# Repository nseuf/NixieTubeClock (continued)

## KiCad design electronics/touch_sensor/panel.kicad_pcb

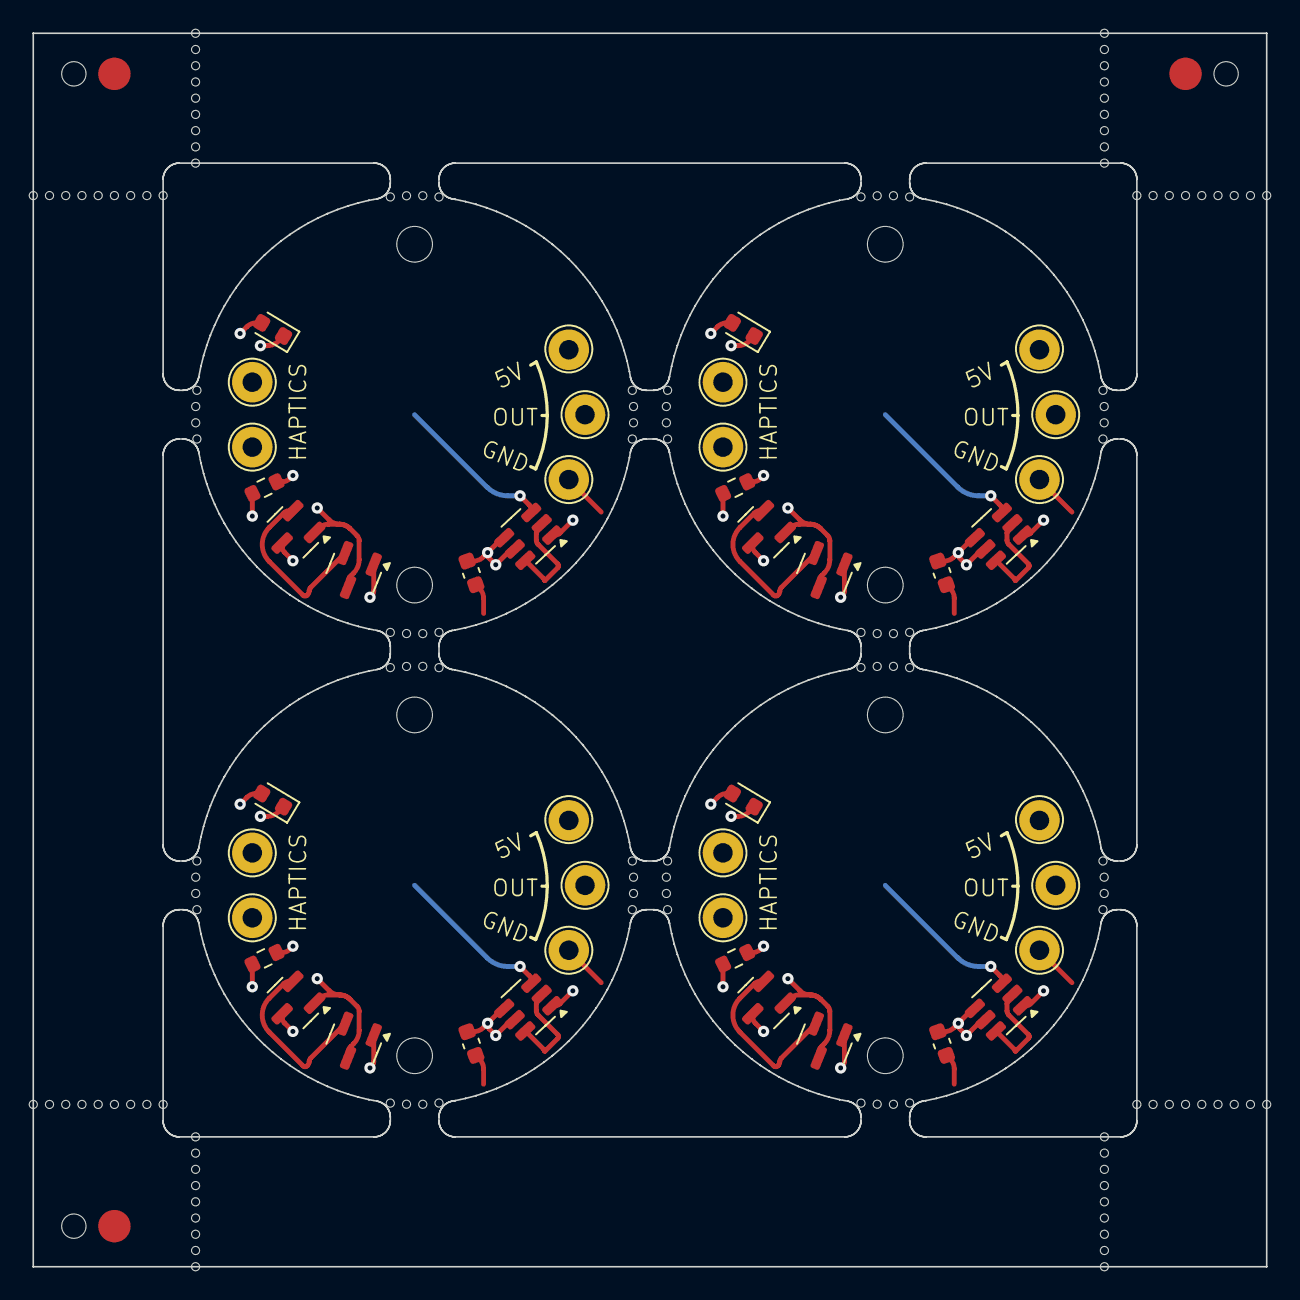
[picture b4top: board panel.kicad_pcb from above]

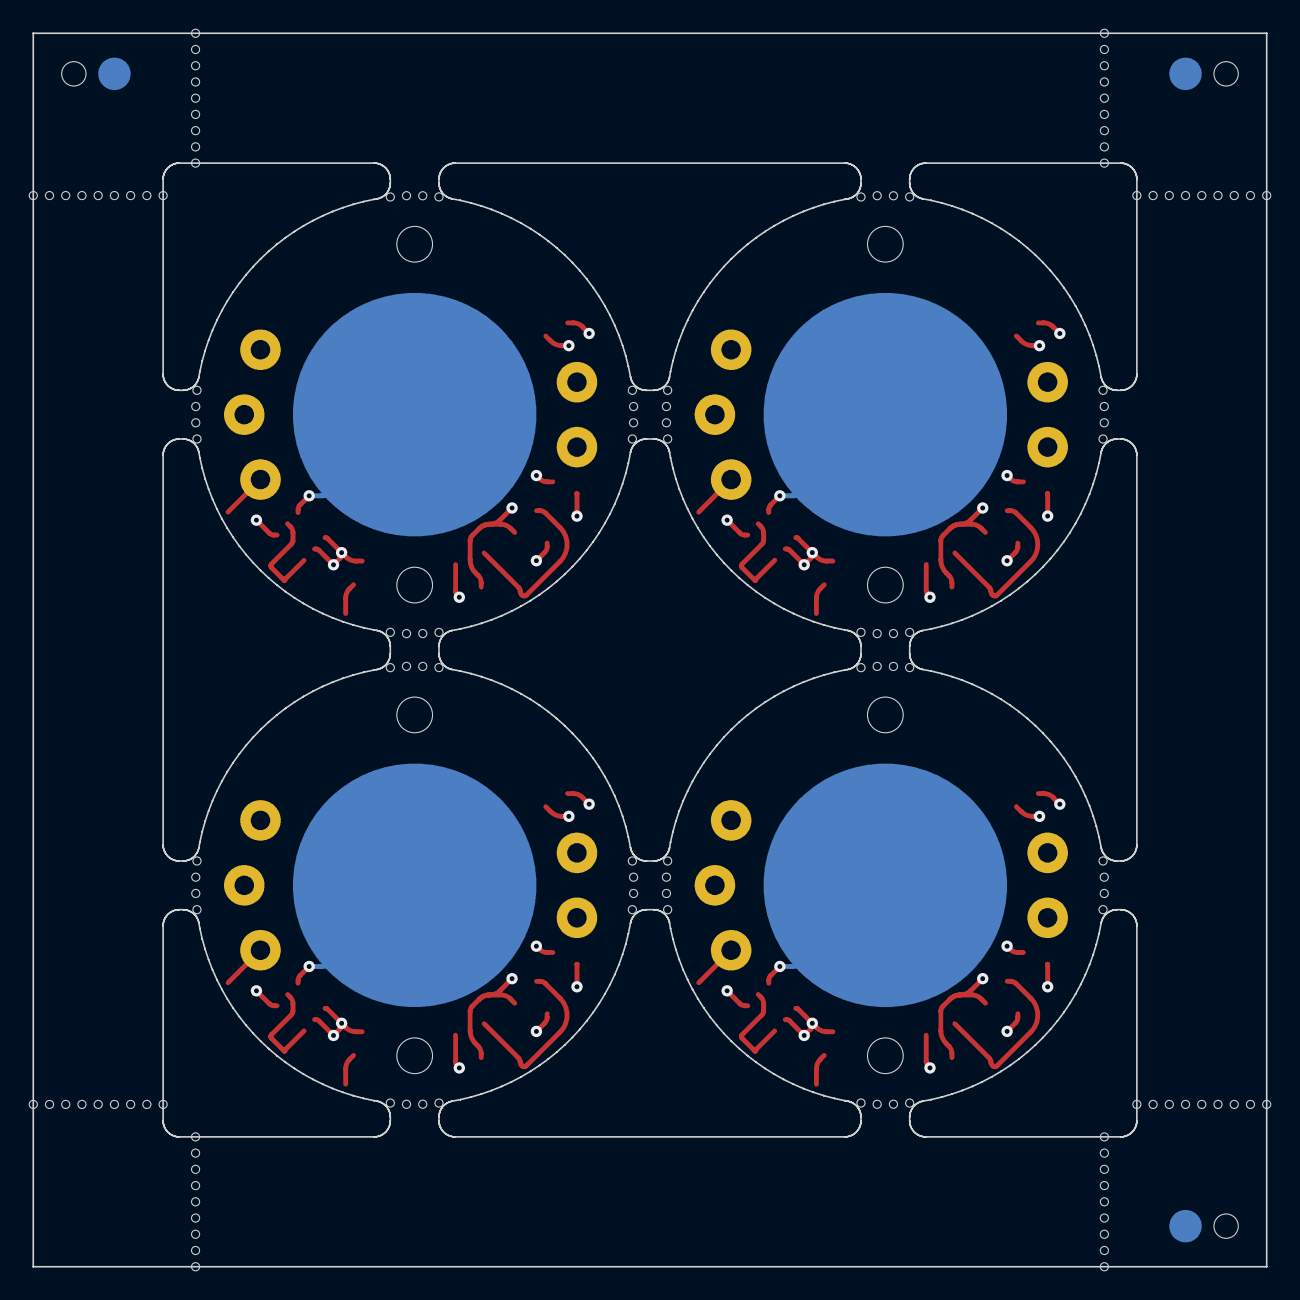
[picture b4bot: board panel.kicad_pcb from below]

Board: 4 copper layers, 76.0 x 76.0 mm, 201 parts (7 on the bottom side), 28 nets.

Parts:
C2, C2#2, C2#3, C2#4: 100n; C_0603_1608Metric
D1, D1#2, D1#3, D1#4: LED; D_0603_1608Metric
H1, H1#2, H1#3, H1#4, H2, H2#2, H2#3, H2#4: MountingHole; MountingHole_2.2mm_M2_ISO7380
KiKit_FID_B_1, KiKit_FID_B_2, KiKit_FID_B_3: Fiducial
KiKit_FID_T_1, KiKit_FID_T_2, KiKit_FID_T_3: Fiducial
KiKit_MB_1_1, KiKit_MB_1_2, KiKit_MB_1_3, KiKit_MB_1_4, KiKit_MB_2_1, KiKit_MB_2_2, KiKit_MB_2_3, KiKit_MB_2_4, KiKit_MB_3_1, KiKit_MB_3_2, KiKit_MB_3_3, KiKit_MB_3_4, KiKit_MB_4_1, KiKit_MB_4_2, KiKit_MB_4_3, KiKit_MB_4_4, KiKit_MB_5_1, KiKit_MB_5_2, KiKit_MB_5_3, KiKit_MB_5_4, KiKit_MB_6_1, KiKit_MB_6_2, KiKit_MB_6_3, KiKit_MB_6_4, KiKit_MB_7_1, KiKit_MB_7_2, KiKit_MB_7_3, KiKit_MB_7_4, KiKit_MB_8_1, KiKit_MB_8_2, KiKit_MB_8_3, KiKit_MB_8_4, KiKit_MB_9_1, KiKit_MB_9_2, KiKit_MB_9_3, KiKit_MB_9_4, KiKit_MB_10_1, KiKit_MB_10_2, KiKit_MB_10_3, KiKit_MB_10_4, KiKit_MB_11_1, KiKit_MB_11_2, KiKit_MB_11_3, KiKit_MB_11_4, KiKit_MB_12_1, KiKit_MB_12_2, KiKit_MB_12_3, KiKit_MB_12_4, KiKit_MB_13_1, KiKit_MB_13_2, KiKit_MB_13_3, KiKit_MB_13_4, KiKit_MB_14_1, KiKit_MB_14_2, KiKit_MB_14_3, KiKit_MB_14_4, KiKit_MB_15_1, KiKit_MB_15_2, KiKit_MB_15_3, KiKit_MB_15_4, KiKit_MB_16_1, KiKit_MB_16_2, KiKit_MB_16_3, KiKit_MB_16_4, KiKit_MB_17_1, KiKit_MB_17_2, KiKit_MB_17_3, KiKit_MB_17_4, KiKit_MB_17_5, KiKit_MB_17_6, KiKit_MB_17_7, KiKit_MB_17_8, KiKit_MB_17_9, KiKit_MB_18_1, KiKit_MB_18_2, KiKit_MB_18_3, KiKit_MB_18_4, KiKit_MB_18_5, KiKit_MB_18_6, KiKit_MB_18_7, KiKit_MB_18_8, KiKit_MB_18_9, KiKit_MB_19_1, KiKit_MB_19_2, KiKit_MB_19_3, KiKit_MB_19_4, KiKit_MB_19_5, KiKit_MB_19_6, KiKit_MB_19_7, KiKit_MB_19_8, KiKit_MB_19_9, KiKit_MB_20_1, KiKit_MB_20_2, KiKit_MB_20_3, KiKit_MB_20_4, KiKit_MB_20_5, KiKit_MB_20_6, KiKit_MB_20_7, KiKit_MB_20_8, KiKit_MB_20_9, KiKit_MB_21_1, KiKit_MB_21_2, KiKit_MB_21_3, KiKit_MB_21_4, KiKit_MB_21_5, KiKit_MB_21_6, KiKit_MB_21_7, KiKit_MB_21_8, KiKit_MB_21_9, KiKit_MB_22_1, KiKit_MB_22_2, KiKit_MB_22_3, KiKit_MB_22_4, KiKit_MB_22_5, KiKit_MB_22_6, KiKit_MB_22_7, KiKit_MB_22_8, KiKit_MB_22_9, KiKit_MB_23_1, KiKit_MB_23_2, KiKit_MB_23_3, KiKit_MB_23_4, KiKit_MB_23_5, KiKit_MB_23_6, KiKit_MB_23_7, KiKit_MB_23_8, KiKit_MB_23_9, KiKit_MB_24_1, KiKit_MB_24_2, KiKit_MB_24_3, KiKit_MB_24_4, KiKit_MB_24_5, KiKit_MB_24_6, KiKit_MB_24_7, KiKit_MB_24_8, KiKit_MB_24_9: NPTH
KiKit_TO_1, KiKit_TO_2, KiKit_TO_3: NPTH
Q1, Q1#2, Q1#3, Q1#4, Q2, Q2#2, Q2#3, Q2#4: BSS127S; SOT-23
R1, R1#2, R1#3, R1#4: 2k; R_0603_1608Metric
T1, T1#2, T1#3, T1#4: TouchPad
TP1, TP1#2, TP1#3, TP1#4, TP2, TP2#2, TP2#3, TP2#4, TP3, TP3#2, TP3#3, TP3#4, TP4, TP4#2, TP4#3, TP4#4, TP5, TP5#2, TP5#3, TP5#4: TestPoint; TestPoint_THTPad_D2.5mm_Drill1.2mm
U1, U1#2, U1#3, U1#4: SOT-23-6

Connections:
Board_0-+5V: C2#3.1, R1#2.1, TP1#3.1, TP4#3.1, U1#2.4 (AHLB), U1#2.5 (VDD)
Board_0-/Output: Q2.1 (G), TP2#3.1, U1#2.1 (OUT)
Board_0-/Sens: T1#2.1 (Touch), U1#2.3 (Sensor_In)
Board_0-GND: C2#3.2, Q1#2.2 (S), Q2.2 (S), TP3.1, U1#2.2 (GND), U1#2.6 (TOG)
Board_0-Net-(D1-A): D1.2 (A), TP5#2.1
Board_0-Net-(D1-K): D1.1 (K), Q1#2.3 (D)
Board_0-Net-(Q1-G): Q1#2.1 (G), Q2.3 (D), R1#2.2
Board_1-+5V: C2#2.1, R1#4.1, TP1#4.1, TP4#2.1, U1#4.4 (AHLB), U1#4.5 (VDD)
Board_1-/Output: Q2#4.1 (G), TP2#4.1, U1#4.1 (OUT)
Board_1-/Sens: T1#3.1 (Touch), U1#4.3 (Sensor_In)
Board_1-GND: C2#2.2, Q1#3.2 (S), Q2#4.2 (S), TP3#4.1, U1#4.2 (GND), U1#4.6 (TOG)
Board_1-Net-(D1-A): D1#2.2 (A), TP5.1
Board_1-Net-(D1-K): D1#2.1 (K), Q1#3.3 (D)
Board_1-Net-(Q1-G): Q1#3.1 (G), Q2#4.3 (D), R1#4.2
Board_2-+5V: C2#4.1, R1.1, TP1#2.1, TP4#4.1, U1#3.4 (AHLB), U1#3.5 (VDD)
Board_2-/Output: Q2#3.1 (G), TP2#2.1, U1#3.1 (OUT)
Board_2-/Sens: T1#4.1 (Touch), U1#3.3 (Sensor_In)
Board_2-GND: C2#4.2, Q1.2 (S), Q2#3.2 (S), TP3#2.1, U1#3.2 (GND), U1#3.6 (TOG)
Board_2-Net-(D1-A): D1#4.2 (A), TP5#4.1
Board_2-Net-(D1-K): D1#4.1 (K), Q1.3 (D)
Board_2-Net-(Q1-G): Q1.1 (G), Q2#3.3 (D), R1.2
Board_3-+5V: C2.1, R1#3.1, TP1.1, TP4.1, U1.4 (AHLB), U1.5 (VDD)
Board_3-/Output: Q2#2.1 (G), TP2.1, U1.1 (OUT)
Board_3-/Sens: T1.1 (Touch), U1.3 (Sensor_In)
Board_3-GND: C2.2, Q1#4.2 (S), Q2#2.2 (S), TP3#3.1, U1.2 (GND), U1.6 (TOG)
Board_3-Net-(D1-A): D1#3.2 (A), TP5#3.1
Board_3-Net-(D1-K): D1#3.1 (K), Q1#4.3 (D)
Board_3-Net-(Q1-G): Q1#4.1 (G), Q2#2.3 (D), R1#3.2

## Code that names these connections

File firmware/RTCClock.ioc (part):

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Mcu.Name=STM32G070RBTx
Mcu.Package=LQFP64
Mcu.UserName=STM32G070RBTx
PA13.Mode=Serial_Wire
PA13.Signal=SYS_SWDIO
PA14-BOOT0.Mode=Serial_Wire
PA14-BOOT0.Signal=SYS_SWCLK
PA2.Mode=Asynchronous
PA2.Signal=USART2_TX
PA3.Mode=Asynchronous
PA3.Signal=USART2_RX
PA5.Mode=TX_Only_Simplex_Unidirect_Master
PA5.Signal=SPI1_SCK
PA6.GPIOParameters=GPIO_Speed
PA6.GPIO_Speed=GPIO_SPEED_FREQ_HIGH
PA6.Signal=GPIO_Output
PA7.Mode=TX_Only_Simplex_Unidirect_Master
PA7.Signal=SPI1_MOSI
PC12.Signal=GPIO_Output
PC14-OSC32_IN\ (PC14).Mode=LSE-External-Oscillator
PC14-OSC32_IN\ (PC14).Signal=RCC_OSC32_IN
PC15-OSC32_OUT\ (PC15).Mode=LSE-External-Oscillator
PC15-OSC32_OUT\ (PC15).Signal=RCC_OSC32_OUT
PC4.Mode=Asynchronous
PC4.Signal=USART1_TX
PC5.Mode=Asynchronous
PC5.Signal=USART1_RX
RCC.HSE_VALUE=8000000
RCC.SYSCLKFreq_VALUE=64000000
RCC.SYSCLKSource=RCC_SYSCLKSOURCE_PLLCLK
board=NUCLEO-G070RB
boardIOC=true

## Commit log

2025-08-10 test commit
2025-08-10 prototype firmware
2025-08-10 pcb firmware
2025-08-10 created pcbs
2025-08-10 updated pcb
2025-08-10 removed panels
2025-08-10 created housings
2025-09-24 added clock assembly drawings
2025-11-16 Redesigned the touch pcb holder
2025-11-16 Added second part of the pcb holder
2025-11-16 fixed passthrough circuit
2025-11-16 Rename 2025.06.11.Cock.PCB Holder Part2.STL to 2025.06.11.Clock.PCB Holder Part2.STL
2025-11-20 Added production files
2025-11-29 Added features
2026-01-13 Update part
2026-04-08 Updated cleaning cycle
2026-04-10 Overhaul
2026-04-12 Add user manual
